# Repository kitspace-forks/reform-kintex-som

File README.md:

# MNT Reform Kintex-7 SoM (MNT RKX7)

This is the open hardware system-on-module featuring the Xilinx/AMD Kintex-7 FPGA (XC7K160T or XC7K325T) and 2GB DDR3 RAM. It can be used as an alternative to the main processor module in the [MNT Reform open hardware laptop](https://www.crowdsupply.com/mnt/reform) or in any other custom device. The idea is to test synthesized open cores such as [CORE-V CVA6](https://github.com/openhwgroup/cva6) (RISC-V), [LiteX](https://github.com/enjoy-digital/litex) (multi-architecture), [LibreSOC](https://libre-soc.org/) (OpenPOWER) in a real laptop. True emulation of vintage computer architectures in a laptop form factor is possible as well.

The module was designed by Lukas F. Hartmann (mntmn) of [MNT Research GmbH](https://mntre.com).

## Status

In September 2022 we assembled and brought up the second revision of the module (D-2) which fixes some problems found in the first revision. We were able to run a full RISC-V Linux desktop on the new module, integrated in the MNT Reform laptop shell. We are using the XC7K325T-FFG676 FPGA. For details, see [the MNT Reform Kintex-7 SoM Showcase](https://mntre.com/media/reform_md/2022-09-29-rkx7-showcase.html).

Changes from D-1:

- The power sequencing IC was missing pullups on the outputs.
- The DDR3 memory routing was completely redone for a less congested layout and avoiding crosstalk. This fixed some address bus errors of the first version.
- The TC358778XBG MIPI encoder was removed. Instead, 24-bit parallel RGB, clocks and extra GPIOs are routed out to a new 50 pin FPC header. This makes the module more flexibly usable.
- We designed a new adapter PCB featuring the Analogix ANX9807 RGB to eDP chip. We are able to successfully drive MNT Reform's eDP Full HD display.
- The TUSB1310ZAY USB3/2 PHY was removed as it is EOL, expensive and there was is no available XHCI host implementation that could drive it. Instead, USB1/2 pads are now driven directly by the FPGA. This works well with the SpinalHDL OHCI host controller which is supported by LiteX.
- 8 FPGA additional pads were broken out to an array of square test points.
- The JTAG header pitch was increased to 2mm for easier access.

The design was created using [KiCAD, a free and open source EDA program](https://www.kicad.org/).

## Specs

- FPGA: [Xilinx Kintex-7](https://www.xilinx.com/products/silicon-devices/fpga/kintex-7.html) XC7K160T-FFG676 or pin-compatible family members. We are using XC7K325T-FFG676 in our tests.
- Memory: 2GB DDR3 (2x Micron IS43TR16512B-125KBLI in 32-bit topology)
- 100 MHz main clock oscillator
- HDMI 1.4 (Full HD) implemented via Sii9022 encoder
- 1 GBit Ethernet via KSZ9031RNX PHY
- 2x PCIe lanes connected to GTX transceivers
- 1x USB3 connected to GTX transceiver
- 3x UART, 2x I2C, 1x SAI, 1x PWM backlight ports connected to FPGA fabric
- 128 MBit configuration flash (Winbond W25Q128JVSIM)
- JTAG header
- 6 synchronous buck converters powered by single 5V input
- Size: 68x67.5mm, 200 pin SO-DIMM card edge (mates with TE 1717254-1 or TE 1473005-1)
- Schematics: [PDF](reform-kintex-schematics.pdf)

## Copyright

All hardware design work in this repository is © 2021-2022 [MNT Research GmbH](https://mntre.com), Berlin, Germany.

## License

All hardware sources are licensed under the [CERN Open Hardware Licence Version 2 - Strongly Reciprocal](https://ohwr.org/project/cernohl/wikis/uploads/002d0b7d5066e6b3829168730237bddb/cern_ohl_s_v2.txt).

## Funding

This project [is made possible through funding by NLNet](https://nlnet.nl/project/MNT-Reform/). Thanks!

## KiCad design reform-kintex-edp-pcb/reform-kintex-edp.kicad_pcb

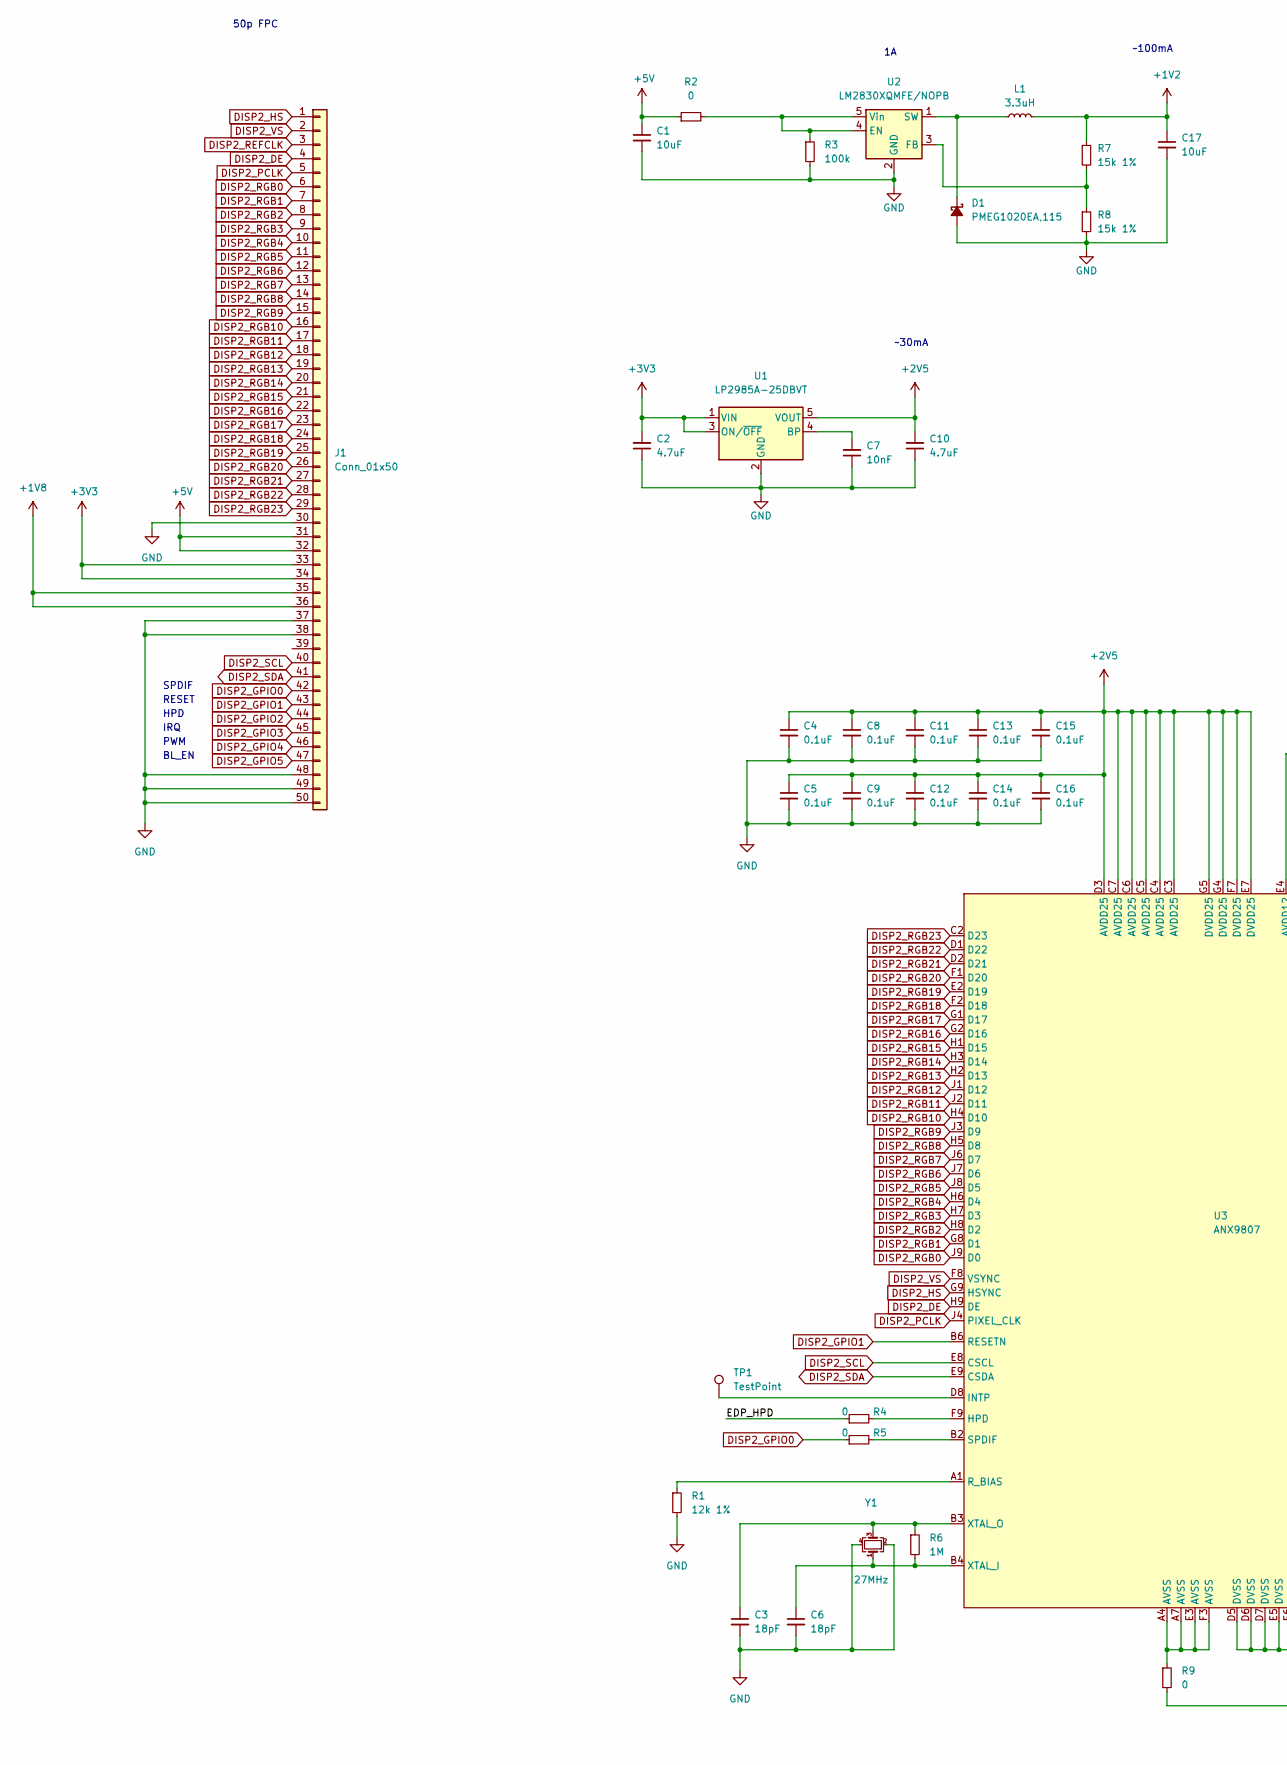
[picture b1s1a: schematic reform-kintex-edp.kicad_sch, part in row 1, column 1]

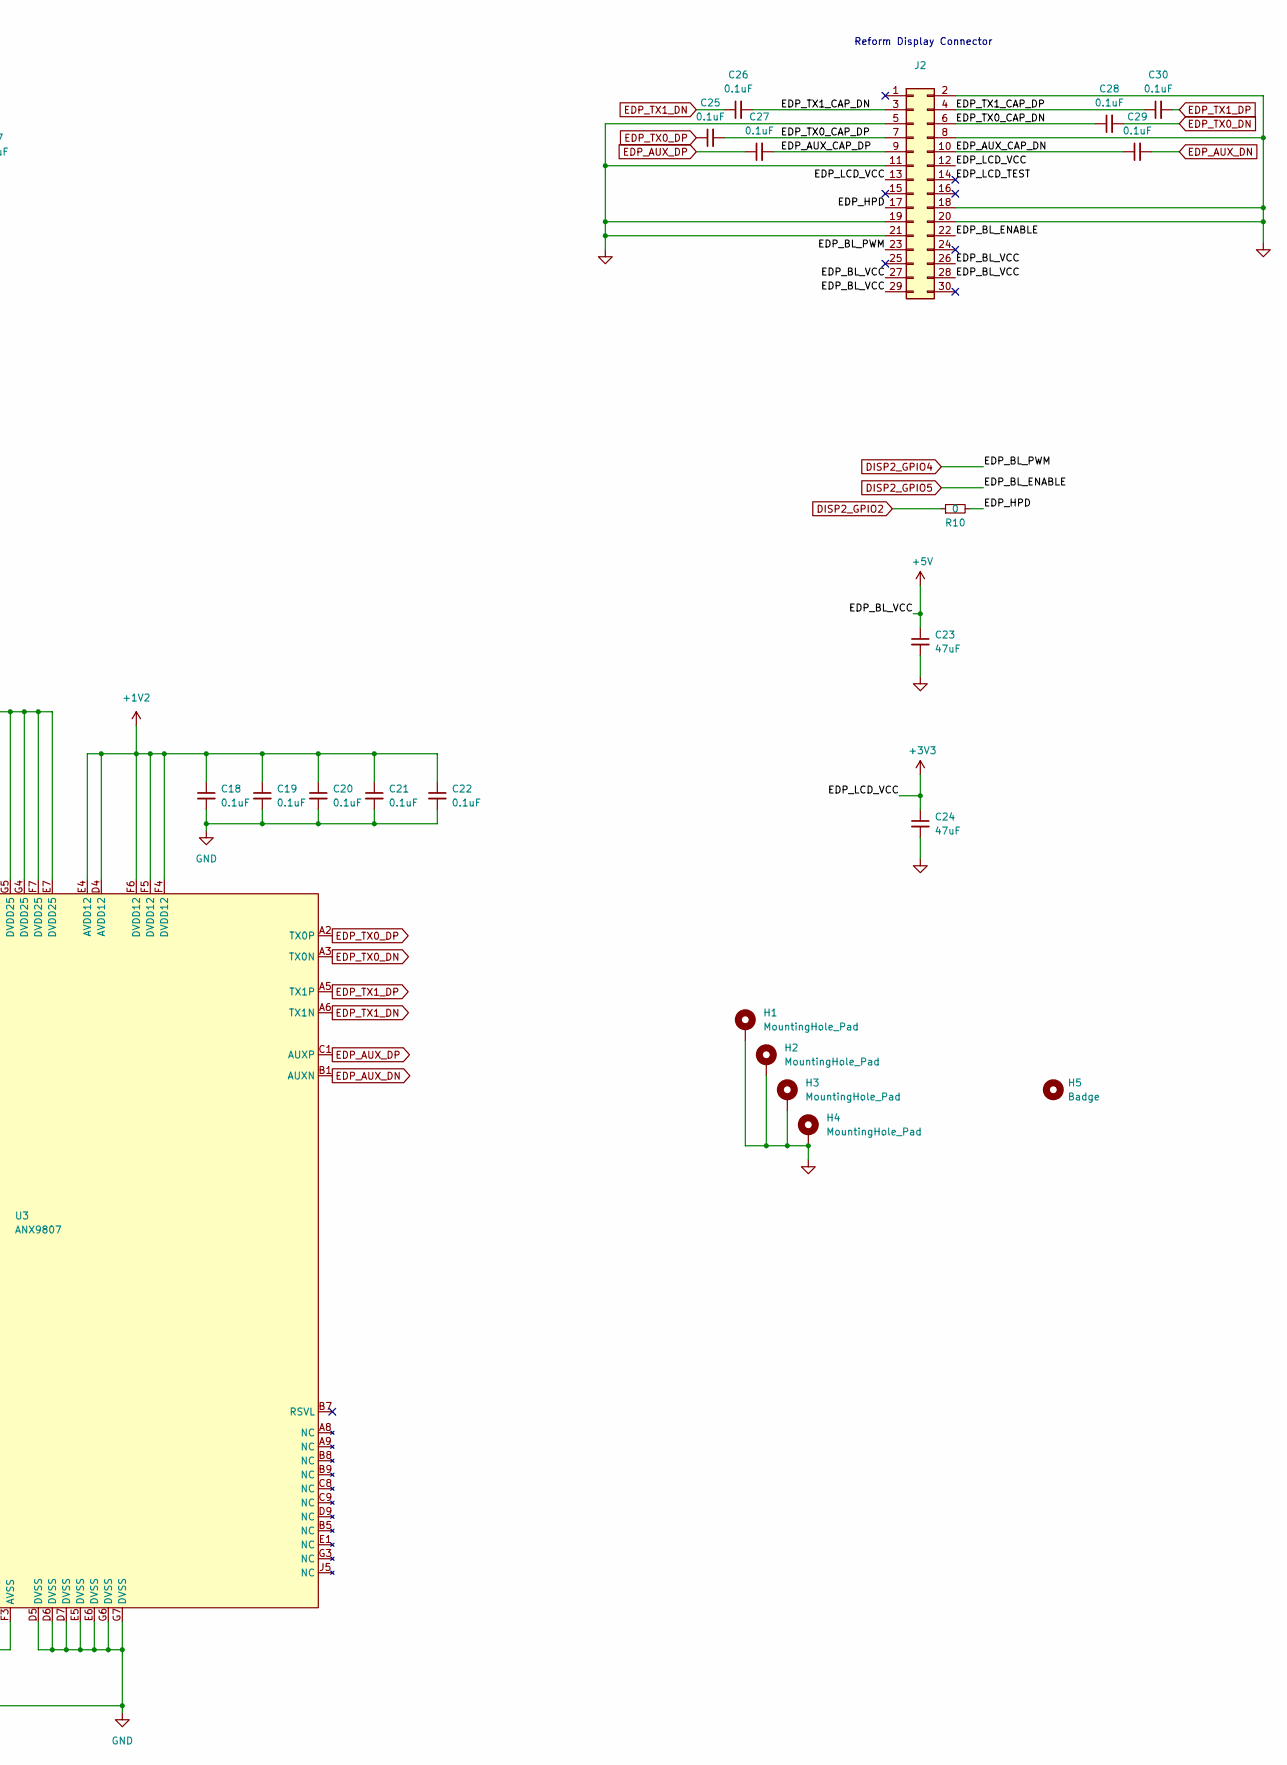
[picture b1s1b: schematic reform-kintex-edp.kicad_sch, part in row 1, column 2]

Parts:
C1, C17: 10uF; C_0603_1608Metric; LCSC C86295
C2, C10: 4.7uF; C_0603_1608Metric
C3, C6: 18pF; C_0603_1608Metric
C4, C5, C8, C9, C11, C12, C13, C14, C15, C16, C18, C19, C20, C21, C22, C25, C26, C27, C28, C29, C30: 0.1uF; C_0402_1005Metric
C7: 10nF; C_0603_1608Metric
C23, C24: 47uF; C_0805_2012Metric
D1: PMEG1020EA,115; D_SOD-323; LCSC C426863
H1, H2, H3, H4: MountingHole_Pad; MountingHole_2.2mm_M2_DIN965_Pad
H5: Badge; mnt-rgb-edp-badge
J1: Conn_01x50; Hirose_FH12-50S-0.5SH_1x50-1MP_P0.50mm_Horizontal
J2: PinHeader_2x15_P2.00mm_Vertical
L1: 3.3uH; L_1210_3225Metric; LCSC C337905
R1: 12k 1%; R_0603_1608Metric
R2, R4, R5, R9, R10: 0; R_0603_1608Metric; LCSC C242160
R3: 100k; R_0603_1608Metric; LCSC C60491
R6: 1M; R_0603_1608Metric
R7, R8: 15k 1%; R_0603_1608Metric
TP1: TestPoint; TestPoint_Pad_D1.0mm
U1: LP2985A-25DBVT; SOT-23-5
U2: LM2830XQMFE/NOPB; SOT-23-5; LCSC C2072452
U3: ANX9807; BGA-ANX-81
Y1: 27MHz; Crystal_SMD_3225-4Pin_3.2x2.5mm; MPN FL2700102Z

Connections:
+1V2: C17.1, C18.1, C19.1, C20.1, C21.1, C22.1, L1.2, R7.1, U3.D4 (AVDD12), U3.E4 (AVDD12), U3.F4 (DVDD12), U3.F5 (DVDD12), U3.F6 (DVDD12)
+1V8: J1.35, J1.36
+2V5: C4.1, C5.1, C8.1, C9.1, C10.2, C11.1, C12.1, C13.1, C14.1, C15.1, C16.1, U1.5 (VOUT), U3.C3 (AVDD25), U3.C4 (AVDD25), U3.C5 (AVDD25), U3.C6 (AVDD25), U3.C7 (AVDD25), U3.D3 (AVDD25), U3.E7 (DVDD25), U3.F7 (DVDD25), U3.G4 (DVDD25), U3.G5 (DVDD25)
+3V3: C2.2, C24.1, J1.33, J1.34, J2.12, J2.13, U1.1 (VIN), U1.3 (ON/~OFF)
+5V: C1.1, C23.1, J1.31, J1.32, J2.26, J2.27, J2.28, J2.29, R2.1
/EDP_AUX_CAP_DN: C29.1, J2.10
/EDP_AUX_CAP_DP: C27.2, J2.9
/EDP_HPD: J2.17, R4.1, R10.2
/EDP_LCD_TEST: J2.14
/EDP_TX0_CAP_DN: C28.1, J2.6
/EDP_TX0_CAP_DP: C25.2, J2.7
/EDP_TX1_CAP_DN: C26.2, J2.3
/EDP_TX1_CAP_DP: C30.1, J2.4
DISP2_DE: J1.4, U3.H9 (DE)
DISP2_GPIO0: J1.42, R5.1
DISP2_GPIO1: J1.43, U3.B6 (RESETN)
DISP2_GPIO2: J1.44, R10.1
DISP2_GPIO3: J1.45
DISP2_GPIO4: J1.46, J2.23
DISP2_GPIO5: J1.47, J2.22
DISP2_HS: J1.1, U3.G9 (HSYNC)
DISP2_PCLK: J1.5, U3.J4 (PIXEL_CLK)
DISP2_REFCLK: J1.3
DISP2_RGB0: J1.6, U3.J9 (D0)
DISP2_RGB1: J1.7, U3.G8 (D1)
DISP2_RGB2: J1.8, U3.H8 (D2)
DISP2_RGB3: J1.9, U3.H7 (D3)
DISP2_RGB4: J1.10, U3.H6 (D4)
DISP2_RGB5: J1.11, U3.J8 (D5)
DISP2_RGB6: J1.12, U3.J7 (D6)
DISP2_RGB7: J1.13, U3.J6 (D7)
DISP2_RGB8: J1.14, U3.H5 (D8)
DISP2_RGB9: J1.15, U3.J3 (D9)
DISP2_RGB10: J1.16, U3.H4 (D10)
DISP2_RGB11: J1.17, U3.J2 (D11)
DISP2_RGB12: J1.18, U3.J1 (D12)
DISP2_RGB13: J1.19, U3.H2 (D13)
DISP2_RGB14: J1.20, U3.H3 (D14)
DISP2_RGB15: J1.21, U3.H1 (D15)
DISP2_RGB16: J1.22, U3.G2 (D16)
DISP2_RGB17: J1.23, U3.G1 (D17)
DISP2_RGB18: J1.24, U3.F2 (D18)
DISP2_RGB19: J1.25, U3.E2 (D19)
DISP2_RGB20: J1.26, U3.F1 (D20)
DISP2_RGB21: J1.27, U3.D2 (D21)
DISP2_RGB22: J1.28, U3.D1 (D22)
DISP2_RGB23: J1.29, U3.C2 (D23)
DISP2_SCL: J1.40, U3.E8 (CSCL)
DISP2_SDA: J1.41, U3.E9 (CSDA)
DISP2_VS: J1.2, U3.F8 (VSYNC)
EDP_AUX_DN: C29.2, U3.B1 (AUXN)
EDP_AUX_DP: C27.1, U3.C1 (AUXP)
EDP_TX0_DN: C28.2, U3.A3 (TX0N)
EDP_TX0_DP: C25.1, U3.A2 (TX0P)
EDP_TX1_DN: C26.1, U3.A6 (TX1N)
EDP_TX1_DP: C30.2, U3.A5 (TX1P)
unnamed: C3.1, R6.1, U3.B3 (XTAL_O), Y1.3
unnamed: C6.1, R6.2, U3.B4 (XTAL_I), Y1.1
unnamed: C7.2, U1.4 (BP)
unnamed: D1.1 (K), L1.1, U2.1 (SW)
unnamed: R1.1, U3.A1 (R_BIAS)
unnamed: R2.2, R3.1, U2.4 (EN), U2.5 (Vin)
unnamed: R4.2, U3.F9 (HPD)
unnamed: R5.2, U3.B2 (SPDIF)
unnamed: R7.2, R8.1, U2.3 (FB)
unnamed: R9.1, U3.A4 (AVSS), U3.A7 (AVSS), U3.E3 (AVSS), U3.F3 (AVSS)
unnamed: TP1.1, U3.D8 (INTP)

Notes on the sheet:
BL_EN
~30mA
PWM
IRQ
~100mA
50p FPC
SPDIF
RESET
Reform Display Connector
HPD

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
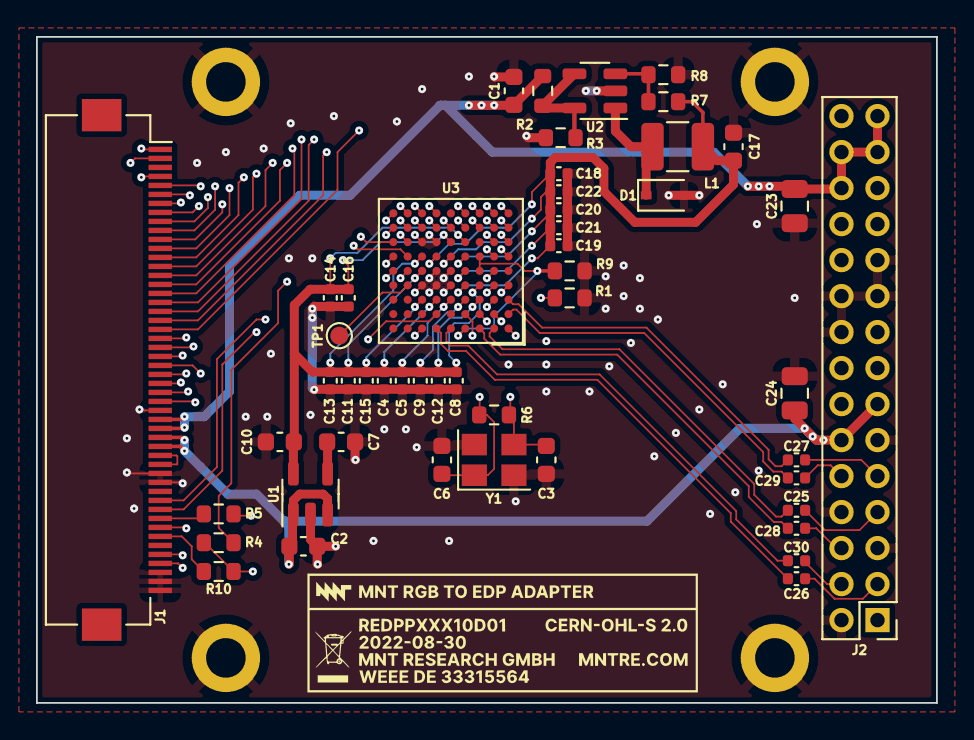
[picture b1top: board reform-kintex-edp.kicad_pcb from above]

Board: 4 copper layers, 50.0 x 37.0 mm, 54 parts (0 on the bottom side), 65 nets.
